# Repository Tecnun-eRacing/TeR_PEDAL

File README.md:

# TeR_PEDAL
The drivers Input Module Sensor, built to fit FSG rules, it provides the vehicle 
data about:
- Brake Pressure
- APPS (Accelerator Pedal Position Sensor)
- Steering Sensor
## Features
- The module is able to self calibrate itself through a series of commands trough CAN 2.0
- Implausible range detection in all sensors + Safety set-zero
- Storage of calibration values in the internal EEPROM for persistance

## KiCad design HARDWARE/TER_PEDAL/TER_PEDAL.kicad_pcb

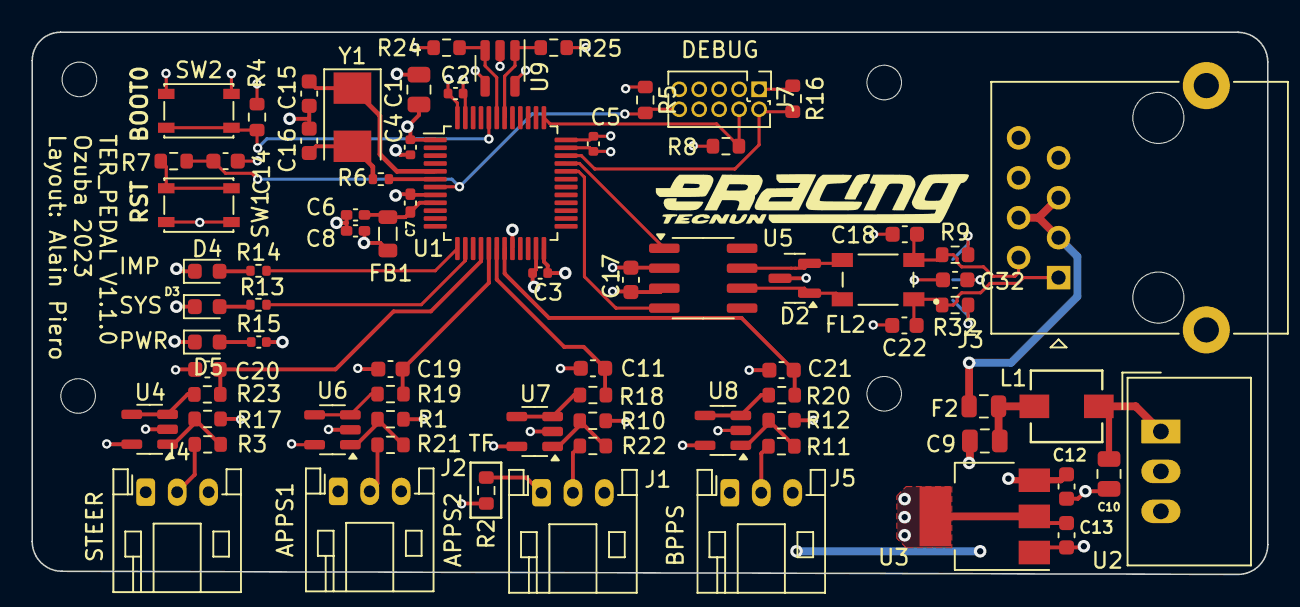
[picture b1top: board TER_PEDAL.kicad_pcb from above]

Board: 4 copper layers, 78.6 x 34.5 mm, 80 parts (1 on the bottom side), 48 nets.

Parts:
C1: 10u; C_0805_2012Metric
C2, C3, C4, C5: 100n; C_0402_1005Metric
C6: 10n; C_0402_1005Metric_Pad0.74x0.62mm_HandSolder
C7, C8: 1u; C_0402_1005Metric_Pad0.74x0.62mm_HandSolder
C9, C10: 10 µF; C_0805_2012Metric
C11, C19, C20, C21: 160n; C_0603_1608Metric
C12, C13: 10u; C_0603_1608Metric
C14, C17: 100n; C_0603_1608Metric
C15, C16, C18, C22: 10p; C_0603_1608Metric
C32: 4.7nF; C_0603_1608Metric
D2: NUP2105L; SOT-23
D3: SYS; LED_0603_1608Metric
D4: IMP; LED_0603_1608Metric
D5: PWR; LED_0603_1608Metric
F2: 500ma; Fuse_0805_2012Metric
FB1: 120R; L_0805_2012Metric
FL2: ACT45B-510-2P-TL003; FIL_ACT45B-510-2P-TL003
H1, H2, H3, H4: MountingHole; MountingHole_2.2mm_M2
J1: APPS_2; JST_PH_S3B-PH-K_1x03_P2.00mm_Horizontal
J2, J4: APPS_1; JST_PH_S3B-PH-K_1x03_P2.00mm_Horizontal
J3: RJ45_Shielded; RJ45_Ninigi_GE
J5: BPPS_1; JST_PH_S3B-PH-K_1x03_P2.00mm_Horizontal
J7: DEBUG; PinHeader_2x05_P1.27mm_Vertical
JP2: SolderJumper_3_Open; SolderJumper-3_P1.3mm_Open_Pad1.0x1.5mm
L1: TCK-141; IND_TCK-141_TRP
R1, R10, R12, R17: 9.1k; R_0603_1608Metric
R2: 0R; R_0603_1608Metric
R3, R11, R21, R22: 4.7k; R_0603_1608Metric
R4, R24, R25: 10k; R_0603_1608Metric
R5, R8, R16: 100k; R_0603_1608Metric
R6: 300R; R_0402_1005Metric
R7: 100R; R_0603_1608Metric
R9, R32: 120R; R_0603_1608Metric
R13, R14: 120R; R_0402_1005Metric
R15: 120R; C_0402_1005Metric
R18, R19, R20, R23: 100; R_0603_1608Metric
SW1: RST; SW_SPST_PTS810
SW2: BOOT0; SW_SPST_PTS810
U1: STM32F103C8Tx; LQFP-48_7x7mm_P0.5mm
U2: TSR_1-2450; Converter_DCDC_TRACO_TSR-1_THT
U3: LM1117MP-3.3; SOT-223-3_TabPin2
U4, U6, U7, U8: LM321; SOT-23-5
U5: TCAN332; SOIC-8_3.9x4.9mm_P1.27mm
U9: AT24CS02-STUM; SOT-23-5
Y1: 8mHz; Crystal_SMD_5032-2Pin_5.0x3.2mm

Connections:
+3.3V: C1.1, C2.1, C3.1, C4.1, C5.1, C8.1, C13.1, C17.2, FB1.2, J7.1 (VTref), R5.1, R15.2, R16.1, R24.1, R25.1, SW2.2 (B), U1.1 (VBAT), U1.24 (VDD), U1.36 (VDD), U1.48 (VDD), U3.2 (VO), U4.5 (V+), U5.3 (VCC), U6.5 (V+), U7.5 (V+), U8.5 (V+), U9.4 (VCC)
+3.3VADC: C6.1, C7.1, FB1.1, U1.9 (VDDA)
+5V: C12.1, J2.1, J4.1, J5.1, R2.1, U2.3 (Vout), U3.3 (VI)
+24V: F2.1, J3.3, J3.4, J3.5
/CAN/CAN+: C18.2, FL2.2, J3.2, R9.1
/CAN/CAN-: C22.1, FL2.1, J3.1, R32.2
/CAN/CAN_RX: U1.32 (PA11), U5.4 (RXD)
/CAN/CAN_TX: U1.33 (PA12), U5.1 (TXD)
/CAN/can+: D2.2 (K), FL2.3, U5.7 (CANH)
/CAN/can-: D2.1 (K), FL2.4, U5.6 (CANL)
/EEPROM/SCL: R25.2, U1.42 (PB6), U9.1 (SCL)
/EEPROM/SDA: R24.2, U1.43 (PB7), U9.3 (SDA)
/IMP_LED: R14.2, U1.13 (PA3)
/MICRO/APPS_1_ADC: C19.1, R19.2, U1.17 (PA7)
/MICRO/APPS_2_ADC: C11.1, R18.2, U1.18 (PB0)
/MICRO/BOOT0: R4.1, SW2.1 (A), U1.44 (BOOT0)
/MICRO/BPPS_ADC: C21.1, R20.2, U1.19 (PB1)
/MICRO/NRST: C14.1, J7.10 (~RESET), R5.2, R7.2, U1.7 (NRST)
/MICRO/OSC_IN: C15.2, U1.5 (PD0), Y1.1
/MICRO/OSC_OUT: R6.1, U1.6 (PD1)
/MICRO/STEER_ADC: C20.1, R23.2, U1.16 (PA6)
/MICRO/SWCLK: J7.4 (SWCLK/TCK), R8.1, U1.37 (PA14)
/MICRO/SWDIO: J7.2 (SWDIO/TMS), R16.2, U1.34 (PA13)
/SENSORS/Brake: J5.2, R11.1
/SENSORS/SENS_1: J2.2, R21.2
/SENSORS/SENS_2: J1.2, R22.2
/SYS: R13.2, U1.14 (PA4)
GND: C1.2, C2.2, C3.2, C4.2, C5.2, C6.2, C7.2, C8.2, C9.2, C10.2, C11.2, C12.2, C13.2, C14.2, C15.1, C16.2, C17.1, C18.1, C19.2, C20.2, C21.2, C22.2, C32.2, D2.3 (A), D3.1 (K), D4.1 (K), D5.1 (K), J1.3, J2.3, J3.6, J3.7, J3.8, J3.SH, J4.3, J5.3, J7.3 (GND), J7.5 (GND), J7.9 (GNDDetect), R1.1, R4.2, R8.2, R10.1, R12.2, R17.1, SW1.1 (A), U1.8 (VSSA), U1.20 (PB2), U1.23 (VSS), U1.35 (VSS), U1.47 (VSS), U2.2 (GND), U3.1 (GND), U4.2 (V-), U5.2 (GND), U6.2 (V-), U7.2 (V-), U8.2 (V-), U9.2 (GND), U9.5 (WP)
unnamed: C9.1, F2.2, L1.2
unnamed: C16.1, R6.2, Y1.2
unnamed: D3.2 (A), R13.1
unnamed: D4.2 (A), R14.1
unnamed: D5.2 (A), R15.1
unnamed: J1.1, R2.2
unnamed: J4.2, R3.2
unnamed: JP2.1 (A), R9.2
unnamed: JP2.3 (B), R32.1
unnamed: C32.1, JP2.2 (C)
unnamed: R7.1, SW1.2 (B)
unnamed: C10.1, L1.1, U2.1 (Vin)
unnamed: R3.1, R17.2, U4.1 (+)
unnamed: R23.1, U4.3 (-), U4.4
unnamed: R1.2, R21.1, U6.1 (+)
unnamed: R19.1, U6.3 (-), U6.4
unnamed: R10.2, R22.1, U7.1 (+)
unnamed: R18.1, U7.3 (-), U7.4
unnamed: R11.2, R12.1, U8.1 (+)
unnamed: R20.1, U8.3 (-), U8.4

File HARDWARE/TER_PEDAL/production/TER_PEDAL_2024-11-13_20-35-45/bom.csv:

Designator,Footprint,Quantity,Value,LCSC Part #
C1,0805,1,10u,
"C10, C9",0805,2,10 µF,
"C11, C19, C20, C21",0603,4,160n,
"C12, C13",0603,2,10u,
"C14, C17",0603,2,100n,
"C15, C16, C18, C22",0603,4,10p,
"C2, C3, C4, C5",0402,4,100n,
C32,0603,1,4.7nF,
C6,0402,1,10n,
"C7, C8",0402,2,1u,
D2,SOT-23,1,NUP2105L,
D3,0603,1,SYS,
D4,0603,1,IMP,
D5,0603,1,PWR,
F2,0805,1,500ma,
FB1,0805,1,120R,
FL2,FIL_ACT45B-510-2P-TL003,1,ACT45B-510-2P-TL003,
"H1, H2, H3, H4",MountingHole_2.2mm_M2,4,MountingHole,
J1,JST_PH_S3B-PH-K_1x03_P2.00mm_Horizontal,1,APPS_2,
"J2, J4",JST_PH_S3B-PH-K_1x03_P2.00mm_Horizontal,2,APPS_1,
J3,RJ45_Ninigi_GE,1,RJ45_Shielded,
J5,JST_PH_S3B-PH-K_1x03_P2.00mm_Horizontal,1,BPPS_1,
J7,PinHeader_2x05_P1.27mm_Vertical,1,DEBUG,
JP2,SolderJumper-3_P1.3mm_Open_Pad1.0x1.5mm,1,SolderJumper_3_Open,
L1,IND_TCK-141_TRP,1,TCK-141,
"R1, R10, R12, R17",0603,4,9.1k,
"R11, R21, R22, R3",0603,4,4.7k,
"R13, R14, R15",0402,3,120R,
"R16, R5, R8",0603,3,100k,
"R18, R19, R20, R23",0603,4,100,
R2,0603,1,0R,
"R24, R25, R4",0603,3,10k,
"R32, R9",0603,2,120R,
R6,0402,1,300R,
R7,0603,1,100R,
SW1,SW_SPST_PTS810,1,RST,
SW2,SW_SPST_PTS810,1,BOOT0,
U1,LQFP-48_7x7mm_P0.5mm,1,STM32F103C8Tx,
U2,Converter_DCDC_TRACO_TSR-1_THT,1,TSR_1-2450,
U3,SOT-223-3_TabPin2,1,LM1117MP-3.3,
"U4, U6, U7, U8",SOT-23-5,4,LM321,
U5,SOIC-8_3.9x4.9mm_P1.27mm,1,TCAN332,
U9,SOT-23-5,1,AT24CS02-STUM,
Y1,Crystal_SMD_5032-2Pin_5.0x3.2mm,1,8mHz,

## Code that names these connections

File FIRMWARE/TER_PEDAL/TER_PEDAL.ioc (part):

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Mcu.Name=STM32F103C(8-B)Tx
Mcu.Package=LQFP48
Mcu.UserName=STM32F103C8Tx
PA11.Mode=CAN_Activate
PA11.Signal=CAN_RX
PA12.Mode=CAN_Activate
PA12.Signal=CAN_TX
PA13.Mode=Serial_Wire
PA13.Signal=SYS_JTMS-SWDIO
PA14.Mode=Serial_Wire
PA14.Signal=SYS_JTCK-SWCLK
PA3.GPIOParameters=GPIO_Label
PA3.GPIO_Label=IMP_LED
PA3.Signal=GPIO_Output
PA4.GPIOParameters=GPIO_Label
PA4.GPIO_Label=SYS
PA4.Signal=GPIO_Output
PA6.GPIOParameters=GPIO_Label
PA6.GPIO_Label=STEER
PA6.Signal=ADCx_IN6
PA7.GPIOParameters=GPIO_Label
PA7.GPIO_Label=APPS_1
PA7.Signal=ADCx_IN7
PB0.GPIOParameters=GPIO_Label
PB0.GPIO_Label=APPS_2
PB0.Signal=ADCx_IN8
PB1.GPIOParameters=GPIO_Label
PB1.GPIO_Label=BPPS
PB1.Signal=ADCx_IN9
PB6.Mode=I2C
PB6.Signal=I2C1_SCL
PB7.Mode=I2C
PB7.Signal=I2C1_SDA
PD0-OSC_IN.Mode=HSE-External-Oscillator
PD0-OSC_IN.Signal=RCC_OSC_IN
PD1-OSC_OUT.Mode=HSE-External-Oscillator
PD1-OSC_OUT.Signal=RCC_OSC_OUT
RCC.SYSCLKFreq_VALUE=32000000
RCC.SYSCLKSource=RCC_SYSCLKSOURCE_PLLCLK
board=custom

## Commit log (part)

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2023-04-28 Initial Commit and proof of concept
2023-05-01 Added kicad project, began mcu design and power stage DCDC converters
2023-05-01 Added STM32 related Application notes and datasheet
2023-05-01 Initial Readme
2023-05-01 Added Can transceiver Circuit
2023-05-01 Added Uniport, Debug and began sensors design
2023-05-02 Added Sensors PSU
2023-05-02 Added footprints to existing components
2023-05-04 Finished Initial Schematic
2023-05-04 Started Layout and fixed wrong footprints
2023-05-05 Sized and Fixed even more footprints + Initial layout
2023-05-05 Added Eracing Logo
2023-05-09 Began layout and switched to 4 layer board
2023-05-09 added powerplanes
2023-05-12 Initial Layout Finished
2023-05-16 Changed Pinout and added status leds silkmask
2023-05-18 updated .gitignore
2023-05-18 Added new Database Formats and started ADC troubleshooting
2023-05-19 Added ADC multichannel DMA reads+ APPS Implausability
2023-05-30 Changed code generation options for clarity in main.c and added virtual eeprom library for storing calibration values of the pedals
2023-05-31 Added offset value storage
2023-06-05 Added Rx Message interupt handling and calibration command
2023-06-06 Add DBC as git submodule
2023-06-06 Added includes and source files from DBC folder git submodule
2023-06-06 Updated Imp signal name
2023-06-07 Switched Imp flag to the one from ter dbc and added brake calibration commands
2023-06-07 Fixed bugs and added implausability reset cmd
2023-08-03 Swapped Custom Supply for traco for simplicity
2023-08-03 Added decouple to all sensors and a new steering sensor input
2023-08-03 The RJ45 pinout was incorrect according to the poe standard, started redesign and relocation of the board revision
2023-08-04 Rearranged board
2023-08-10 Added holes, connectors and finished re-layout
2023-08-11 Finished Routing for redisign
2023-08-18 Added IMG to README.md
2023-08-18 Added Labels on silkscreen and, versioning and IMG
2023-08-21 Fixed ferrite bead imposible size to 805
2023-09-02 Quick Fix on the debug conector Bus where it was not connected to 3.3V + Labels
2023-09-03 Adapted Code to V1.0.0 board
2023-09-15 Añadido .STEP
2023-09-17 Bumped Bugfix version and fixed unnecessary BOOT0 pin and rj45 placement
2023-09-27 Fixed bug with ADC conversion where it would not Read properly any signal cause of the addition of steer and forgetting to include it in conversion
2023-10-06 Removed the possibility of the micro entering Error_Handler instead an error in can transmission results in the DBG led turning on
2023-10-29 Accurate rj45 3d model
2023-11-24 Added pull down resistors for adc to prevent floating value when disconnected signals, added LABELS lots of labels
2023-11-24 Added Template to Schematics
2023-11-28 Added Pulldown simulation
2023-12-12 Corrected inputs in code, added steering autocal and verified that calibration sequence works
2023-12-21 Added default value to flash writing if new board, corrected multiple bugs with calibration
2024-02-06 Migrated to new software architecture structure
2024-02-07 Migrated PEDAL to new software architecture
2024-06-05 condensador señal brake
2024-07-09 Enabled avg setting to 0 when implausible
2024-07-10 Añadido AutobusOFF
2024-07-16 Added proper out of range implausablity range
2024-07-23 New Docs
2024-07-23 Removed old hidden files
2024-07-23 añadido margin superior del apps y borrados calibraciones cel bpps
2024-07-25 Cabiado esquematico, falta layout
2024-07-26 Hecho layout
2024-07-26 Quick conversion fix
2024-07-26 Quick float math fix
2024-07-26 Quick fix
2024-07-26 Quick fix again
2024-07-26 Ane y el algebra de BOOL
2024-07-26 Cambiados limites del Freno
2024-07-29 Update pedal.h
    Cambio Epiko del limite de implausability
2024-07-29 Update pedal.c
    Tranquilidad del Espiritu
2024-07-29 Fix int32 thing
2024-08-16 Added voltage followers to sensing, improved can circuitri, improved layout, waiting for routing
2024-09-04 Alimentacion de los sensores de la apps actualizado a 5V
2024-10-04 çMejorado layout
2024-10-20 avanzando
2024-10-21 avanzando layout
2024-10-22 Añadiendo eeprom (no terminado)
2024-10-22 EEPROM añadida
2024-11-02 conectores mas dentro, relayout can
2024-11-13 production
2025-02-05 functional v2 with eeprom
2025-02-05 mejoradas algunas cosas
2025-02-05 mejor libreria, mañana pruebo
2025-02-05 doble seta solucion
2025-02-06 cambiado tamaño de pagina de eeprom
2025-02-10 eeprom funcional, placa testeada en coche
2025-02-10 Added Open Source License
2025-02-10 Improved README and deleted trash
2025-02-10 updated gitignore
2025-02-10 ignore production
2025-02-10 Better gitignored
2025-02-10 More gitignore improvements
2025-02-10 Applied gitignore
2025-02-10 Readded database submodules
2025-04-03 bootloader
2025-04-04 updated bootloader to 8kb
2025-04-11 boot
2025-07-15 Remove build folders
2025-07-15 Changed brake signal size
2025-09-02 ultimo de mi portatil
2025-10-07 velis feliz
2025-10-09 fixed calibration of steering
2026-01-25 traer FIRMWARE desde v2 a MAIN
2026-01-25 submodule fixes
2026-01-25 proyect settings
2026-03-11 Not working code for steering disconnect
2026-04-07 working code for steering disconnect :)
